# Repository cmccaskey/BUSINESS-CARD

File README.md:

# About #
This is a busness card I designed for a career fair that was held at my University. This card utilizes the ATtiny24A microcontroller and the AT42qt1011 Q-Touch IC.

# Hardware History #

## REV C ## 
- This is an updated version of the board that uses a coin cell battery with the solder tabs welded on from the factory. This has proven to be more reliable than the previous self designed battery holder
- This version also included an inverter IC to generate the low level interrupt by hardware directly.
- The ground plane was added back on the bottom side of the PCB to make the card only sensitive to touch on the top side

# Firmware History #

## BC.c ##
- This is the code for the first two versions of the card

## TC.c ##
- This is the code for the third version that utilizes the hardware interrupt

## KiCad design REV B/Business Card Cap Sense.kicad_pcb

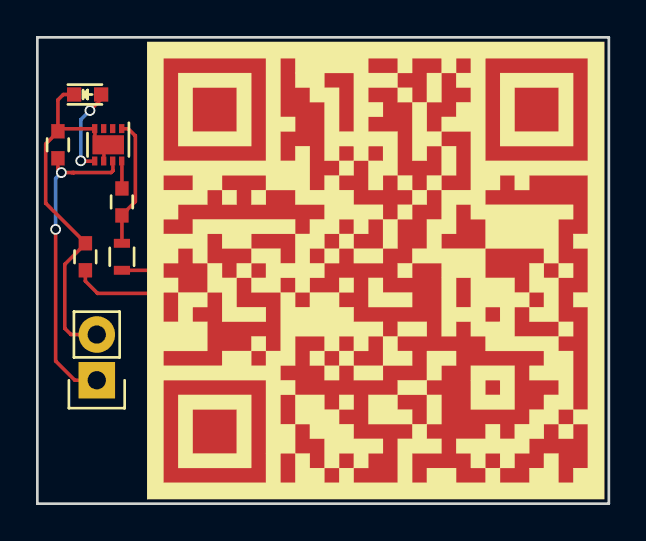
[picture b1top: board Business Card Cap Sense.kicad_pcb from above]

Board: 2 copper layers, 31.8 x 25.9 mm, 8 parts (0 on the bottom side), 6 nets.

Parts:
C2: 1uF; C_0603
C3: 2nF-50nF; C_0603
C4: 5pF-20pF; C_0603
D1: LED_Small; LED_0603
P1: PWR; Pin_Header_Straight_1x02
R1: 1K; R_0603
T1: TOUCH
U2: AT42QT1011; DFN-8-1EP_2x2mm_Pitch0.5mm

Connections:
GND: C2.1, C4.2, D1.1, P1.2, U2.4, U2.6, U2.9
unnamed: C3.1, R1.2, U2.1
unnamed: C3.2, U2.8
unnamed: C4.1, R1.1, T1.1
unnamed: D1.2, U2.5
VCC: C2.2, P1.1, U2.7

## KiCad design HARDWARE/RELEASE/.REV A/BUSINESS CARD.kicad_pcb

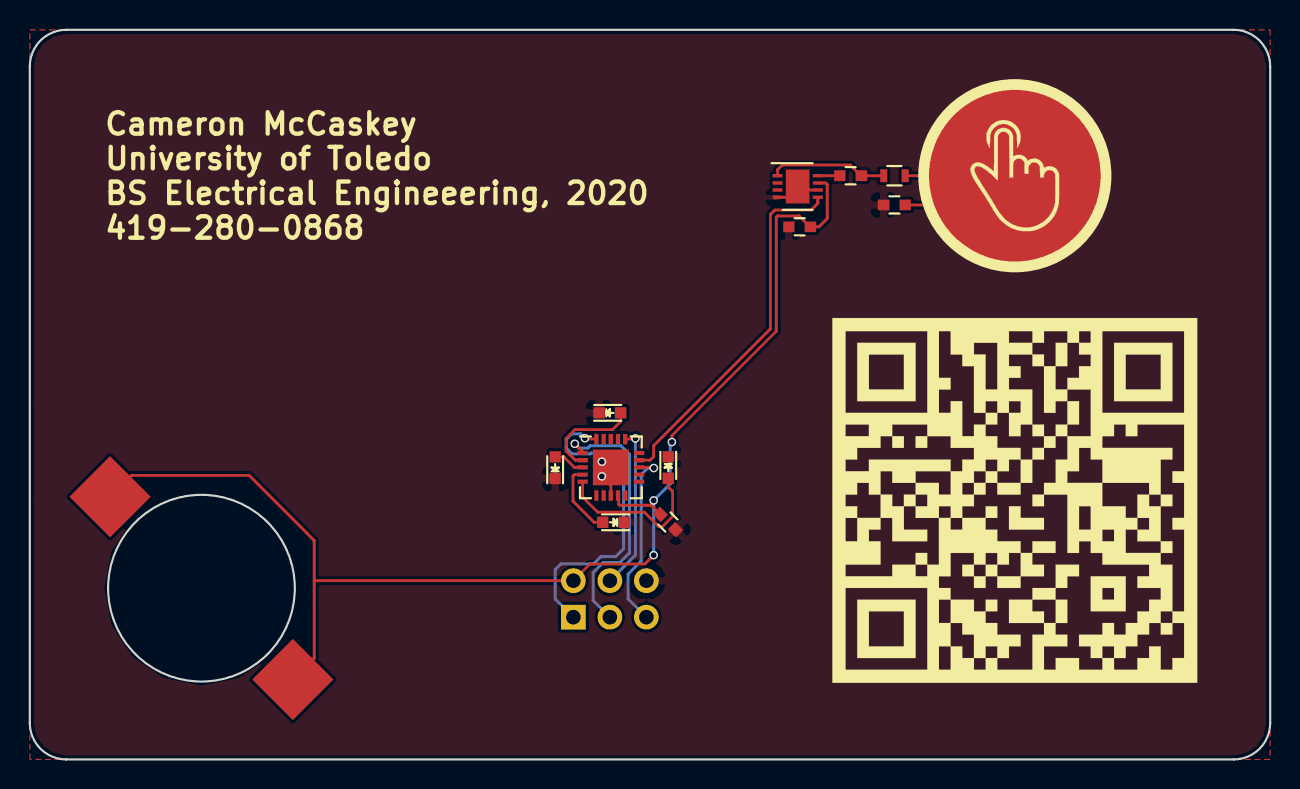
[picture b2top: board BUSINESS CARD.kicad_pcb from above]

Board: 2 copper layers, 86.4 x 50.8 mm, 14 parts (0 on the bottom side), 14 nets.

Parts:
BT1: CR2032; CR1220
C1, C3, C4: C; C_0603
C2: 1uF; C_0603
D1, D2, D3, D4: LED_Small; LED_0603
P1: ICSP
R1: R; R_0603
T1: TOUCH
U1: ATTINY84-M; QFN-20-1EP_4x4mm_Pitch0.5mm
U2: AT42QT1011; DFN-8-1EP_3x3mm_Pitch0.5mm

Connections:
AVR_INT: U1.14, U2.5
GND: BT1.2, C1.2, C2.1, C4.2, D1.1, D2.1, D3.1, D4.1, P1.6, U1.8, U1.21, U2.4, U2.6, U2.9
MISO: P1.1, U1.20
MOSI: P1.4, U1.16
unnamed: C3.1, R1.2, U2.1
unnamed: C3.2, U2.8
unnamed: C4.1, R1.1, T1.1
unnamed: D1.2, U1.5
unnamed: D2.2, U1.4
unnamed: D3.2, U1.3
unnamed: D4.2, U1.2
RST: P1.5, U1.13
SCK: P1.3, U1.1
VCC: BT1.1, C1.1, C2.2, P1.2, U1.9, U2.7

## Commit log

2017-09-27 Initial Commit
    REV B fixes footprint for Q Touch IC. REV B includes new layout for card.
2018-01-01 initial
2018-01-01 folder changes
2018-01-14 fixed MCUCR line in INV.c
2018-01-14 fixed F_CPU in INV.c
2018-07-04 removed old rev
2018-07-04 removed old rev with new gitignore
2018-07-04 update of gitignore
2018-07-05 rotated gif
